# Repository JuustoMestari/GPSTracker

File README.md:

GPSTracker
==========

## Arduino

Arduino Pro mini 3.3V 8Mhz ( copy )

### Libraries

#### SoftwareSerial

In order to run the code properly, you need to modify **SoftwareSerial.h** (Arduino\libraries\SoftwareSerial) before compiling.
At line **42** change _SS_MAX_RX_BUFF to 256 : `#define _SS_MAX_RX_BUFF 256 `

#### NeoPixel

Please use the library in this repo. It has been modified to use Analog Port as well (Leds are connected to Analog 5)
If you want to make the modification yourself, replace all **PORTB** by **PORTC**  in Adafruit_NeoPixel.cpp (You won't be able to use the library with ports 8 to 13 tho...)
* Make a backup of the original file and use the modified version only to compile for this project !

[See here for port manipulation](http://www.arduino.cc/en/Reference/PortManipulation)

## Hardware

### TP4056

* Green LED ON - Red LED Blink -> **No battery**
* RED LED ON -> **Loading**
* GREEN LED ON -> **Loaded**

The module in this project uses a mini USB connector but micro USB versions are available on eBay.

[Module test](http://lygte-info.dk/review/Review%20Charger%20TP4056%20UK.html)

## Datasheets

## Eagle

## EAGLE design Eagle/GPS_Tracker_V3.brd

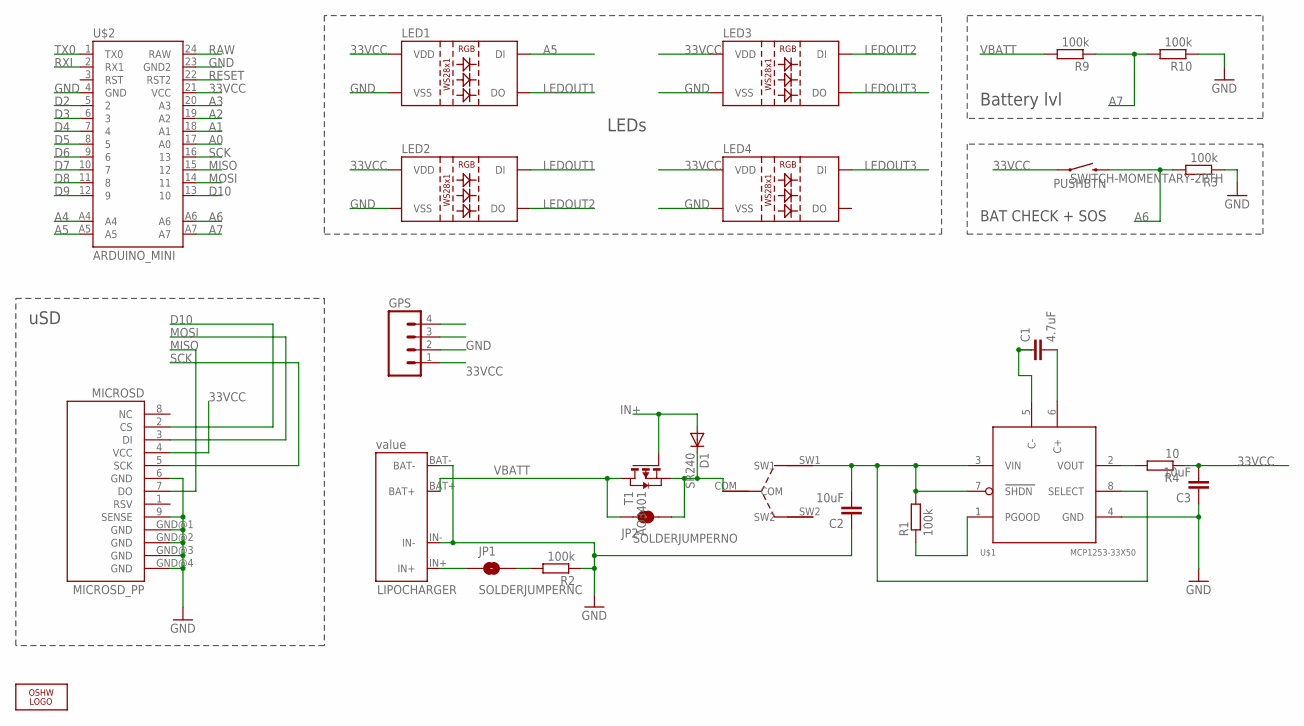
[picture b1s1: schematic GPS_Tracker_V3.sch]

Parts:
C1: 4.7uF; C1206
C2, C3: 10uF; C1206
D1: SR240; DO214AC
GPS: M04PTH; 1X04
JP1: SOLDERJUMPERNC; SJ_2S
JP2: SOLDERJUMPERNO; SJ_2S-NO
LED1, LED2, LED3, LED4: LED-TRICOLOR-5050-ICWS2811; LED-TRICOLOR-5050-IC
LIPOCHARGER: LIPO_CHARGER
LOGO1: OSHW_LOGO_10MILX0200-NT; OSHW_10X200_NOTEXT
MICROSD: MICROSD_PP
PUSHBTN: SWITCH-MOMENTARY-2PTH; TACTILE-PTH
R1, R2, R3, R9, R10: 100k; R1206
R4: 10; R1206
SW: SWITCHDAV; 5IL3MM
T1: AO3401; SOT-23
U$1: MCP1253-33X50; MSOP8
U$2: ARDUINO_MINI

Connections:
33VCC: C3.2, GPS.1, LED1.3 (VDD), LED1.5 (VDD), LED2.3 (VDD), LED2.5 (VDD), LED3.3 (VDD), LED3.5 (VDD), LED4.3 (VDD), LED4.5 (VDD), MICROSD.4 (VCC), PUSHBTN.1, R4.1, U$2.21 (VCC)
A0: U$2.17 (A0)
A1: U$2.18 (A1)
A2: U$2.19 (A2)
A3: U$2.20 (A3)
A4: U$2.A4
A5: LED1.2 (DI), U$2.A5
A6: PUSHBTN.3 (2), R3.2, U$2.A6
A7: R9.1, R10.2, U$2.A7
D2: U$2.5 (2)
D3: U$2.6 (3)
D4: U$2.7 (4)
D5: U$2.8 (5)
D6: U$2.9 (6)
D7: U$2.10 (7)
D8: U$2.11 (8)
D9: U$2.12 (9)
D10: MICROSD.2 (CS), U$2.13 (10)
GND: C2.1, C3.1, GPS.2, LED1.6 (VSS), LED2.6 (VSS), LED3.6 (VSS), LED4.6 (VSS), LIPOCHARGER.BAT-, LIPOCHARGER.IN-, MICROSD.6 (GND), MICROSD.9 (SENSE), MICROSD.GND@1 (GND), MICROSD.GND@2 (GND), MICROSD.GND@3 (GND), MICROSD.GND@4 (GND), R2.1, R3.1, R10.1, U$1.4 (GND), U$2.4 (GND), U$2.23 (GND2)
IN+: D1.A, JP1.2, R2.2, T1.3 (G)
LEDOUT1: LED1.1 (DO), LED2.2 (DI)
LEDOUT2: LED2.1 (DO), LED3.2 (DI)
LEDOUT3: LED3.1 (DO), LED4.2 (DI)
MISO: MICROSD.7 (DO), U$2.15 (12)
MOSI: MICROSD.3 (DI), U$2.14 (11)
unnamed: C2.2, R1.2, SW.SW1, U$1.3 (VIN), U$1.7 (SHDN), U$1.8 (SELECT)
unnamed: C1.1, U$1.5 (C-)
unnamed: C1.2, U$1.6 (C+)
unnamed: D1.C, JP2.2, SW.COM, T1.2 (S)
unnamed: R1.1, U$1.1 (PGOOD)
unnamed: R4.2, U$1.2 (VOUT)
unnamed: JP1.1, LIPOCHARGER.IN+
RAW: U$2.24 (RAW)
RESET: U$2.22 (RST2)
RXI: U$2.2 (RX1)
SCK: MICROSD.5 (SCK), U$2.16 (13)
TX0: U$2.1 (TX0)
VBATT: JP2.1, LIPOCHARGER.BAT+, R9.2, T1.1 (D)

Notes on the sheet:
Battery lvl
BAT CHECK + SOS
uSD
LEDs

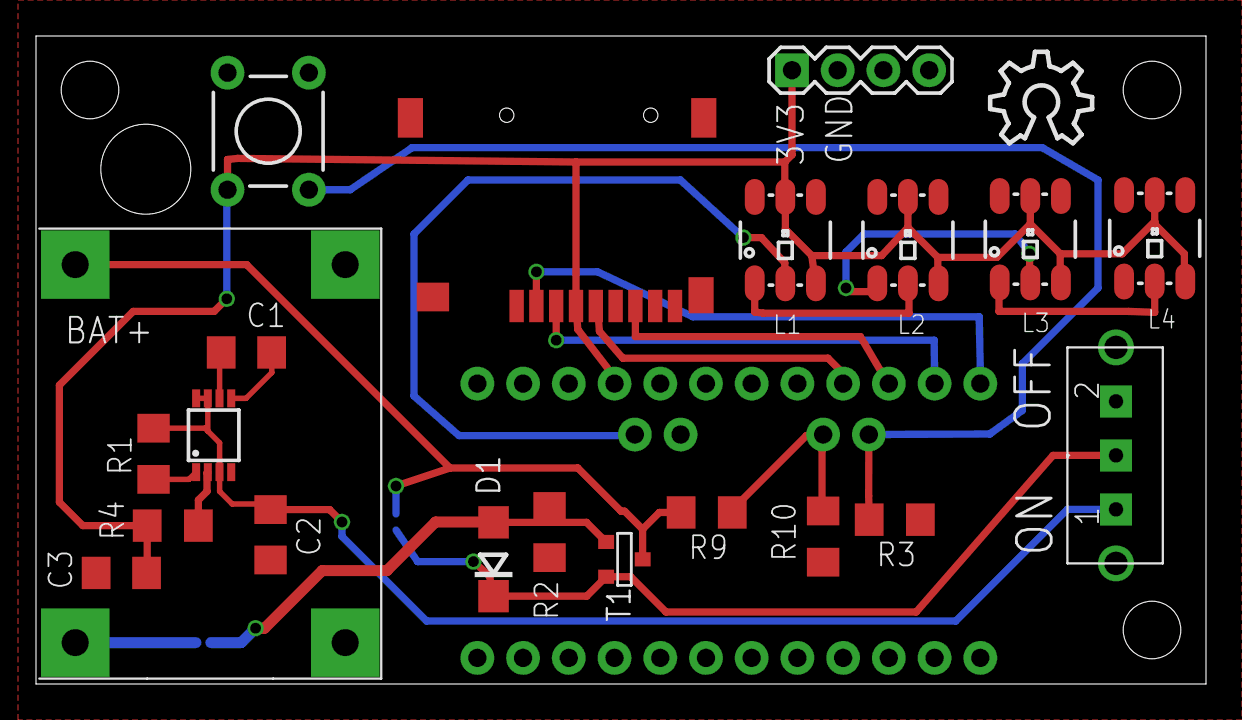
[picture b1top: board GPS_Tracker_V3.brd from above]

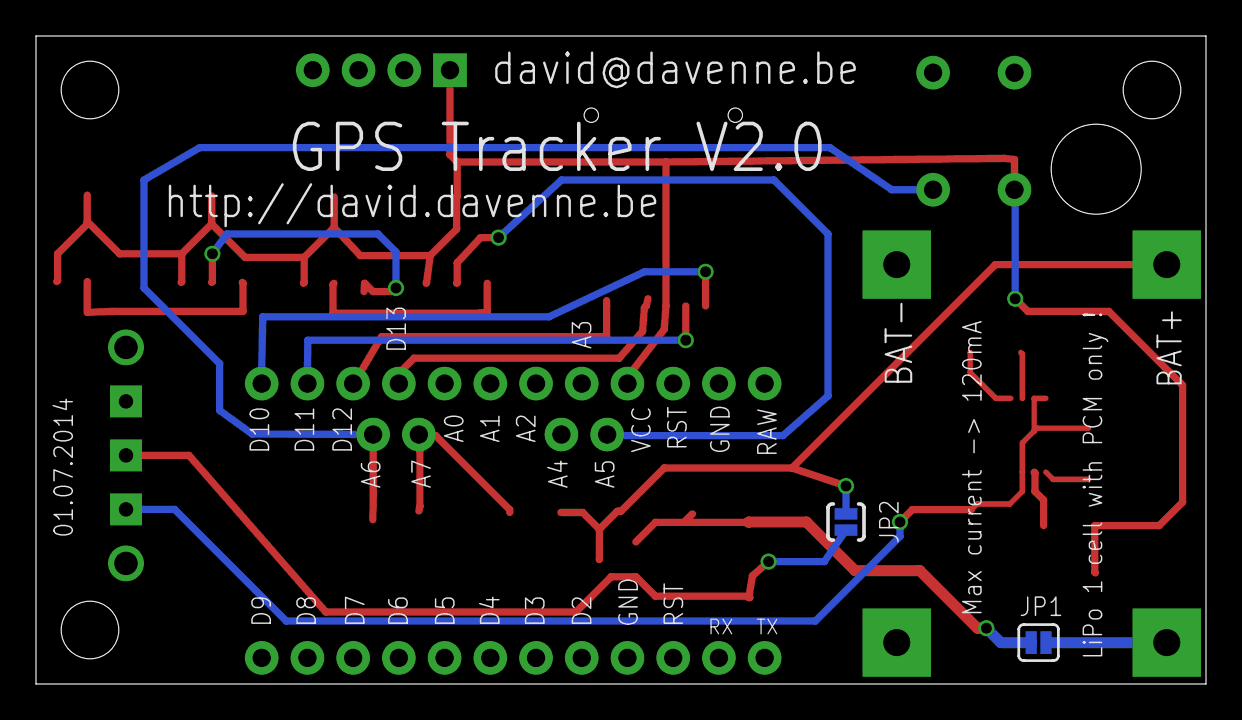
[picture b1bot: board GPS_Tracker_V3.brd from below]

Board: 2 copper layers, 65.0 x 36.0 mm, 25 parts (2 on the bottom side), 21 nets.

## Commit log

2014-07-28 modified Neopixel lib
2014-08-15 Added PNGs

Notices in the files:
parts and their libraries:
SparkFun-Electromechanical: Licensing: CC v3.0 Share-Alike You are welcome to use this library for commercial purposes.
